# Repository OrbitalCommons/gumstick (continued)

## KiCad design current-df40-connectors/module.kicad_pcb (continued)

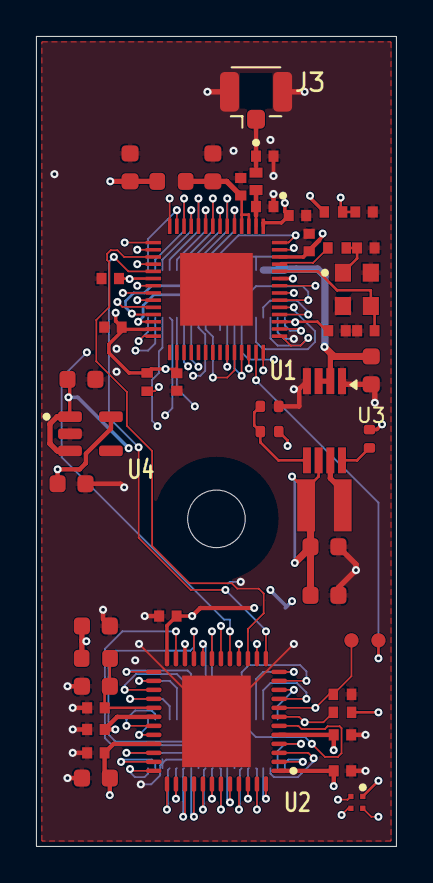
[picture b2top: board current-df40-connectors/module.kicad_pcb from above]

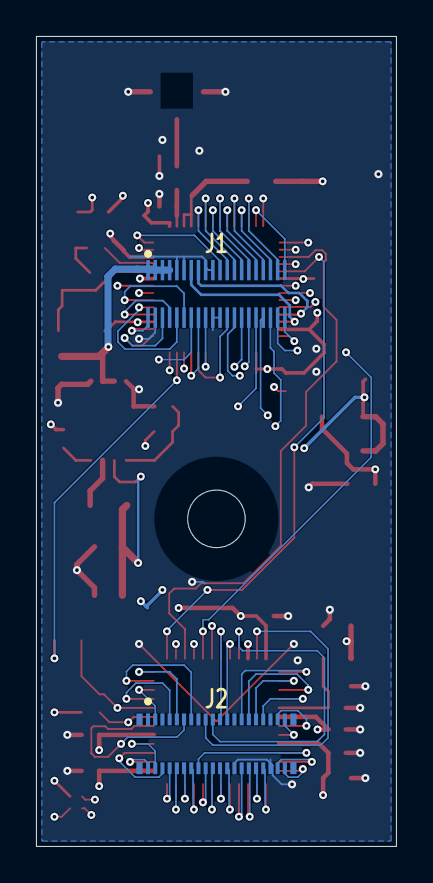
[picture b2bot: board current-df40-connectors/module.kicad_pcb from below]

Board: 4 copper layers, 20.0 x 45.0 mm, 52 parts (2 on the bottom side), 84 nets.

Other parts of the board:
H1: MountingHole_3.2mm_M3

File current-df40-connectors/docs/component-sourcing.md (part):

# Component sourcing

Catalog identities checked 2026-09-23 for the current ESP32-S2 module.
All 50 purchased component placements now have a manufacturer part number
and an LCSC product link (21 unique part numbers). Catalog identity and
package size were checked; this is not a reservation of assembly stock.
Confirm JLCPCB assembly availability and the final land patterns before ordering.

## Corrected imported IDs

- U1: C2841141 is ESP32-S2FH2, not the requested 4 MB part. Use C2840995, ESP32-S2FH4.
- Y1: C555614 is a JGHC crystal. The selected ECS-400-10-36-CKY-TR is C2449947.
- L3: the imported manufacturer part number was a ferrite bead. The 2.2 nH RF inductor is Murata LQG15HS2N2S02D, C86061.
- C33/C34/C43/C45: the old 0402 supplier ID no longer matched their 0603 footprints. These now use the same 10 V, 0603 part as C60.
- C61/C67 are now matched 10 V 0603 output capacitors; C62–C66 retain their selected 50 V parts.

## Selected parts

| References | Manufacturer part | LCSC | Specification |
| --- | --- | --- | --- |
| C1, C2 | GJM1555C1H3R3BB01D | [C76906](https://www.lcsc.com/product-detail/C76906.html) | 0402; 3.3 pF; C0G; 50 V |
| C32 | CL05A105KO5NNNC | [C29266](https://www.lcsc.com/product-detail/C29266.html) | 0402; 1 uF; X5R; 16 V |
| C33, C34, C43, C45, C60 | CL10A106KP8NNNC | [C19702](https://www.lcsc.com/product-detail/C19702.html) | 0603; 10 uF; X5R; 10 V |
| C35, C37, C38, C39, C40, C41, C42, C44, C46, C48, C49, C50, C52 | CL05B104KO5NNNC | [C1525](https://www.lcsc.com/product-detail/C1525.html) | 0402; 100 nF; X7R; 16 V |
| C6, C7 | CL05C120JB5NNNC | [C26406](https://www.lcsc.com/product-detail/C26406.html) | 0402; 12 pF; C0G; 50 V |
| C61, C67 | CL10A226MPCNUBE | [C5355402](https://jlcpcb.com/partdetail/6155917-CL10A226MPCNUBE/C5355402) | 0603; 22 uF each; X5R; 10 V; two in parallel |
| C62, C63, C66 | CL10A105KB8NNNC | [C15849](https://www.lcsc.com/product-detail/C15849.html) | 0603; 1 uF; X5R; 50 V |
| D1 | FC-B1010RGBT-HG | [C158099](https://www.lcsc.com/product-detail/C158099.html) | Common-anode RGB; 1.0 x 1.0 mm |
| J1 | DF40C(2.0)-40DS-0.4V(51) | [C597934](https://www.lcsc.com/product-detail/C597934.html) | 40 contacts; 0.4 mm pitch; receptacle |
| L1, L2 | BLM18KG101TN1D | [C160981](https://www.lcsc.com/product-detail/C160981.html) | 0603; ferrite bead; 100 ohm at 100 MHz |
| L3 | LQG15HS2N2S02D | [C86061](https://www.lcsc.com/product-detail/C86061.html) | 0402; 2.2 nH; RF inductor |
| L4 | XFL3012-222MEC | [C3911432](https://www.lcsc.com/product-detail/C3911432.html) | 3 x 3 mm; 2.2 uH |
| R20, R22, R28, R29, R60, R61 | RC0402FR-0710KL | [C60490](https://www.lcsc.com/product-detail/C60490.html) | 0402; 10 kohm; 1% |
| R3 | 0402WGF0000TCE | [C17168](https://www.lcsc.com/product-detail/C17168.html) | 0402; 0 ohm |
| R62 | RC0402FR-07100KL | [C60491](https://www.lcsc.com/product-detail/C60491.html) | 0402; 100 kohm; 1% |
| U1 | ESP32-S2FH4 | [C2840995](https://www.lcsc.com/product-detail/C2840995.html) | QFN56; 7 x 7 mm; 4 MB flash |
| U2 | ICE40UP5K-SG48I | [C2678152](https://www.lcsc.com/product-detail/C2678152.html) | QFN48; industrial temperature grade |
| U3 | TPS62160DGKR | [C60726](https://www.lcsc.com/product-detail/C60726.html) | VSSOP8; exposed leads; R64/R65 set 3.3 V |
| U4 | TLV75512PDBVR | [C2877864](https://www.lcsc.com/product-detail/C2877864.html) | SOT-23-5; 1.2 V LDO |
| Y1 | ECS-400-10-36-CKY-TR | [C2449947](https://www.lcsc.com/product-detail/C2449947.html) | 2520; 40 MHz; CL 10 pF |

AE1 is a purchased Pulse chip antenna, and H1 is
a drilled mounting hole; none is a purchased assembly component. The M3
screw/spacer and mating motherboard connectors belong to the future carrier BOM.

## ESP32-C3 option

The ESP32-C3 is not a pin-compatible substitute: its QFN32 package is 5 x 5 mm,
whereas ESP32-S2FH4 is QFN56, 7 x 7 mm. A change to C3 requires a new footprint,
pin assignment, power/boot review and routing. Its smaller GPIO budget also
requires reviewing the FPGA link and carrier signals. The current files and
BOM retain the S2 until that architecture decision is made.

Sources: [Espressif ESP32-C3 datasheet](https://documentation.espressif.com/esp32-c3_datasheet_en.html),
[Espressif ESP32-S2 datasheet](https://documentation.espressif.com/esp32-s2_datasheet_en.html).

## Chip antenna option

A ceramic chip antenna could free part of the antenna end, but the entire
manufacturer-defined copper keepout, matching network and carrier clearance
must be compared—not just the component body. No antenna substitution or
outline reduction has been made. See [Johanson antenna layout guidance](https://www.johansontechnology.com/docs/3827/Antenna-2450AT1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

## Procurement follow-up

The exact ECS crystal is currently listed out of stock at LCSC.
[DigiKey lists the same ECS part as XC2666CT-ND](https://www.digikey.com/en/products/detail/ecs-inc/ECS-400-1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,
so it can be sourced without changing the crystal circuit. Arrange the
assembler's supported procurement/consignment method before ordering.
The original C555614 (JGHC S2240000101050JY) has similar catalog frequency,
load and package specifications, but is not silently substituted for ECS.

J2 is now the complementary **DF40C-40DP-0.4V(51)** plug, LCSC
[C424643](https://www.lcsc.com/product-detail/C424643.html). The plug is
manufacturer-listed as mating to J1’s receptacle type. Verify current
stock and JLCPCB assembly availability; prior shared J1/J2 sourcing is obsolete.
TP1/TP2 are bare probe pads and require no purchased parts.

## Smaller buck output capacitors — 2026-09-24

C61's former 0805 is replaced by two matched 0603 capacitors, C61/C67. JLCPCB listed 3,154 in stock (2,642 available to order) when checked; stock must be rechecked at order time. Samsung specifies 1.6 × 0.8 × 0.85 mm, 10 V, ±20%, X5R (−55 to +85 °C). Its typical 25 °C DC-bias curve gives about −55% at 3.3 V: about 10 µF each, or 20 µF combined. Applying −20% initial tolerance and −15% temperature variation as a conservative budgeting exercise gives approximately 13.5 µF combined, not a guaranteed manufacturer minimum. TI TPS62162 Table 2 supports 2.2 µH with 10/22/47 µF nominal ceramic outputs; the pair provides margin over a single small 22 µF part. Bench transient/stability validation remains part of prototype validation.

Sources: [Samsung characteristics](https://product.samsungsem.com/mlcc/CL10A226MPCNUB.do), [TI TPS62162](https://www.ti.com/lit/ds/symlink/tps62162.pdf). The sampled manufacturer DC-bias curve is saved in `capacitor-output-selection.json`.

### Minimum capacitor package

Use 0402 or larger capacitors. C35 is restored to Samsung CL05B104KO5NNNC (C1525), 100 nF, 16 V, X7R, 0402, and moved outward to leave fanout space. Prefer moving components outward over shrinking below 0402. Confirm stock at order.

### Antenna Revision B

AE1 is now purchased Pulse ANT2012LL00R2400A (LCSC C3284792; 363 listed in stock on 2026-09-26); J3 is Hirose U.FL-R-SMT-1(01), supplier pending. R63 is a populated 0402 zero-ohm link: UNI-ROYAL 0402WGF0000TCE, C17168 (JLCPCB Basic listing checked 2026-09-26). Final RF tuning remains pending. C68/C69 are DNP 0402 tuning sites. JP1 is an etched cut/bridge selector, not a purchased component. See antenna/INTEGRATION.md for release gates.

## Current RF revision — external only
AE1, JP1, R63, C68 and C69 are removed. Their preceding sourcing history is superseded. J3 remains Hirose U.FL-R-SMT-1(01), supplier ordering ID pending. No chip antenna or chip-tuning components are purchased.

## Crystal replacement — 2026-09-26
Y1 now uses JGHC S2240000101050, C426970, replacing the unavailable ECS part referenced in the historical table above. LCSC lists 1040 and JLCPCB lists 1069. See crystal-replacement.md for footprint and oscillator validation details.

## Inspectable buck update — 2026-09-26

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
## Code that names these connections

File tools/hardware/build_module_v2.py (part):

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
# ESP32-C6 QFN40 (datasheet v1.5 Table 2-1 / 2-4): no in-package flash; SPI0/1 pins 20-22 and 24-26 go to the external W25Q128 (U4).
# The flash runs from the 3.3 V plane (datasheet: VDD_SPI may be left for other use when the flash has its own supply), so pin 23 is
# unconnected: VDD_SPI sits between the flash data pins and its 0.1/1 uF pair would have no room. QFN40 has GPIO10/11 and no GPIO14: CRESET/CDONE move to GPIO10/11, GPIO18 goes to the connector.
esp_names = {'1': 'ANT', '2': 'VDDA3P3', '3': 'VDDA3P3', '4': 'CHIP_PU', '5': 'VDDPST1', '6': 'GPIO0/XTAL_32K_P', '7': 'GPIO1/XTAL_32K_N',
             '8': 'GPIO2/FSPIQ', '9': 'GPIO3', '10': 'GPIO4/MTMS', '11': 'GPIO5/MTDI', '12': 'GPIO6/MTCK/FSPICLK', '13': 'GPIO7/MTDO/FSPID',
             '14': 'GPIO8', '15': 'GPIO9', '16': 'GPIO10', '17': 'GPIO11', '18': 'GPIO12/USB_D-', '19': 'GPIO13/USB_D+', '20': 'SPICS0',
             '21': 'SPIQ', '22': 'SPIWP', '23': 'VDD_SPI', '24': 'SPIHD', '25': 'SPICLK', '26': 'SPID', '27': 'GPIO15', '28': 'VDDPST2',
             '29': 'GPIO16/U0TXD', '30': 'GPIO17/U0RXD', '31': 'GPIO18', '32': 'GPIO19', '33': 'GPIO20', '34': 'GPIO21', '35': 'GPIO22',
             '36': 'GPIO23', '37': 'VDDA1', '38': 'XTAL_N', '39': 'XTAL_P', '40': 'VDDA2', '41': 'GND'}
esp_pins = {'1': 'RF_IN', '2': 'ESP_VDD3P3', '3': 'ESP_VDD3P3', '4': 'ESP_EN', '5': '+3.3V', '6': 'FPGA_SPI_IO3', '7': 'FPGA_SPI_MOSI',
            '8': 'FPGA_SPI_CS_N', '9': 'FPGA_SPI_SCK', '10': 'ESP_GPIO4', '11': 'ESP_GPIO5', '12': 'FPGA_SPI_MISO', '13': 'FPGA_SPI_IO2',
            '14': 'ESP_GPIO8', '15': 'ESP_GPIO9_BOOT', '16': 'FPGA_CRESET_N', '17': 'FPGA_CDONE', '18': 'USB_D-', '19': 'USB_D+', '20': 'FLASH_CS',
            '21': 'FLASH_DO', '22': 'FLASH_WP', '24': 'FLASH_HD', '25': 'FLASH_CLK', '26': 'FLASH_DI', '27': 'ESP_GPIO15',
            '28': '+3.3V', '29': 'ESP_GPIO16_TXD', '30': 'ESP_GPIO17_RXD', '31': 'ESP_GPIO18', '32': 'ESP_GPIO19', '33': 'ESP_GPIO20',
            '34': 'ESP_GPIO21', '35': 'ESP_GPIO22', '36': 'ESP_GPIO23', '37': '+3.3V', '38': 'XTAL_N', '39': 'XTAL_P', '40': '+3.3V', '41': 'GND'}
esp_types = {k: ('power_in' if n in ('VDDA3P3', 'VDDPST1', 'VDDPST2', 'VDDA1', 'VDDA2', 'GND') else 'power_out' if n == 'VDD_SPI' else 'input' if n in ('CHIP_PU',) else 'passive' if n in ('ANT', 'XTAL_N', 'XTAL_P') else 'bidirectional') for k, n in esp_names.items()}
add('U1', 'ESP32-C6', stdfp('Package_DFN_QFN', 'QFN-40-1EP_5x5mm_P0.4mm_EP3.6x3.6mm', 'QFN-40-1EP_5x5mm_P0.4mm_EP3.3x3.3mm'),
    esp_pins, U1X, U1Y, 0, 'ic', 'ESP32-C6', 'C5364646', esp_names, esp_types)
# 16 MB quad SPI NOR (W25Q128JVPIQ, WSON-8 6x5) in the north-east corner, rotated so DI/CLK/HOLD/VCC face the channel from U1
flash_names = {'1': '/CS', '2': 'DO(IO1)', '3': '/WP(IO2)', '4': 'GND', '5': 'DI(IO0)', '6': 'CLK', '7': '/HOLD(IO3)', '8': 'VCC', '9': 'EP'}
flash_pins = {'1': 'FLASH_CS', '2': 'FLASH_DO', '3': 'FLASH_WP', '4': 'GND', '5': 'FLASH_DI', '6': 'FLASH_CLK', '7': 'FLASH_HD', '8': '+3.3V', '9': 'GND'}
flash_types = {'1': 'input', '2': 'bidirectional', '3': 'bidirectional', '4': 'power_in', '5': 'bidirectional', '6': 'input', '7': 'bidirectional', '8': 'power_in', '9': 'passive'}
add('U4', 'W25Q128JVPIQ', stdfp('Package_SON', 'WSON-8-1EP_6x5mm_P1.27mm_EP3.4x4.3mm', 'WSON-8-1EP_6x5mm_P1.27mm_EP3.4x4.3mm'),
    flash_pins, 118.0, 105.3, -90, 'ic', 'W25Q128JVPIQ', 'C190862', flash_names, flash_types)
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fpga_pins = {}
for k, n in fpga_names.items():
    if n.startswith(('IOB_', 'IOT_')) and 'SPI' not in n: fpga_pins[k] = 'FPGA_' + n
fpga_pins.update({'1': '+3.3V', '5': '+1.2V', '7': 'FPGA_CDONE', '8': 'FPGA_CRESET_N', '14': 'FPGA_SPI_MISO', '15': 'FPGA_SPI_SCK', '16': 'FPGA_SPI_CS_N',
                  '17': 'FPGA_SPI_MOSI', '13': 'FPGA_SPI_IO2', '18': 'FPGA_SPI_IO3', '22': '+3.3V', '24': '+3.3V', '29': '+1.2V_PLL', '30': '+1.2V',
                  '33': '+3.3V', '39': 'FPGA_RGB0', '40': 'FPGA_RGB1', '41': 'FPGA_RGB2', 'PAD': 'GND'})
fpga_types = {k: ('power_in' if n in ('VCCIO_2', 'VCC', 'SPI_VCCIO1', 'VPP_2V5', 'VCCPLL', 'VCCIO_0', 'GND') else 'output' if n == 'CDONE' else 'input' if n == 'CRESET_B' else 'bidirectional') for k, n in fpga_names.items()}
add('U2', 'iCE40UP5K-SG48', v1fp('ICE40-QFN', 'ICE40-QFN'), fpga_pins, U2X, U2Y, 180, 'ic', 'ICE40UP5K-SG48I', 'C2678152', fpga_names, fpga_types)

add('Y1', '40MHz / CL10pF', v1fp('Y1_JGHC_S2240000101050', 'Crystal_2520_4pin'), {'IN/OUT': 'XTAL_P_CRYSTAL', 'OUT/IN': 'XTAL_N', 'GND-A': 'GND', 'GND-B': 'GND'},
    110.4, 107.0, 0, 'xtal', 'S2240000101050', 'C426970', {'IN/OUT': 'IN/OUT', 'OUT/IN': 'OUT/IN', 'GND-A': 'GND', 'GND-B': 'GND'})
add('J3', 'U.FL-R-SMT-1(01)', v1fp('J3_U.FL_Hirose_U.FL-R-SMT-1_Vertical', 'UFL_Vertical'), {'1': 'RF_ANT', '2': 'GND'}, 104.95, 106.5, 90, 'connector', 'U.FL-R-SMT-1(01)', '')
add('TP1', 'FPGA_CRESET_N', v1fp('TestPoint_0p8', 'TestPoint_0p8'), {'1': 'FPGA_CRESET_N'}, 116.8, 122.2, 0, 'testpoint', bom=False)
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cap0402('C1', '1.5pF', 'RF_IN', 'GND', 107.0, 111.7154, 90, '', 'GJM1555C1H1R5WB01D')
ind0402('L3', '2.2nH', 'RF_IN', 'RF_ANT', 105.8, 112.2, 180, 'C86061', 'LQG15HS2N2S02D')
cap0402('C2', '1.5pF', 'RF_ANT', 'GND', 104.35, 111.7154, 90, '', 'GJM1555C1H1R5WB01D')
# crystal north of pins 38/39; at 0.4 mm pitch only 0201 parts fit on the pin lines (L5 on XTAL_P, C39 on VDDA1)
ind0201('L5', '24nH', 'XTAL_P', 'XTAL_P_CRYSTAL', 109.6, 110.15, 90, '', 'LQP03TG24NJ02D')
cap0402('C6', '12pF', 'XTAL_P_CRYSTAL', 'GND', 108.3, 107.29, 90, 'C26406')
cap0402('C7', '12pF', 'XTAL_N', 'GND', 112.6, 106.7096, -90, 'C26406')
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cap0402('C37', '0.1uF', '+3.3V', 'GND', 105.9, 114.2846, -90)        # VDDPST1 pin 5, west of the link columns (pad 1 on the pin-5 line)
res0402('R22', '10k', 'ESP_EN', '+3.3V', 105.9, 118.64, 90)
cap0402('C32', '1uF', 'ESP_EN', 'GND', 105.9, 120.6, -90, 'C29266')
cap0402('C38', '0.1uF', '+3.3V', 'GND', 115.35, 111.15, 90)          # VDDPST2 pin 28, north of the GPIO15/TXD/RXD vias
cap0603('C33', '10uF', '+3.3V', 'GND', 114.0, 105.0, 90)
# flash supply decoupling at U4 pin 8 (+3.3V): 0.1 uF (0201) in the pocket between the HOLD drop and the WP/DO/CS columns;
# C33 (10 uF) sits on the same plane 4 mm west of the chip
cap0201('C68', '0.1uF', '+3.3V', 'GND', 119.585, 109.35, 180)       # pad 1 on the pin-8 drop, 1.4 mm from the pin
res0402('R20', '10k', 'ESP_GPIO9_BOOT', '+3.3V', 115.1, 121.0, -90)    # pad 1 north next to the GPIO9 level via
res0402('R21', '10k', 'ESP_GPIO8', '+3.3V', 114.15, 121.3, -90)

# --- 1.2 V regulator cluster west of the FPGA; FPGA decoupling at its pins.
# U2 at (111,130.5) rotation 180: pins 13-24 top (y 127.0), 25-36 left (x 107.5), 37-48 bottom (y 134.0), 1-12 right (x 114.5).
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res0402('R29', '10k', 'FPGA_CDONE', '+3.3V', 119.5, 123.2, 0)

# ---------------------------------------------------------------- M.2 contacts (custom pinout; see docs/icd-v2-pinout.csv)
GND_CONTACTS = [1, 3, 9, 15, 21, 27, 39, 45, 51, 57, 71, 73, 75]   # 33 now carries ESP_GPIO4
PWR_CONTACTS = [2, 4, 70, 72, 74]
# ESP signals ride a B.Cu bus down the east margin to the even (B.Cu) contacts 6..34; order follows the bus nesting.
esp_contacts = {34: 'ESP_EN', 33: 'ESP_GPIO4', 32: 'ESP_GPIO5', 30: 'ESP_GPIO8', 28: 'ESP_GPIO9_BOOT', 26: 'USB_D-', 24: 'USB_D+', 22: 'ESP_GPIO15',
                20: 'ESP_GPIO16_TXD', 18: 'ESP_GPIO17_RXD', 16: 'ESP_GPIO18', 14: 'ESP_GPIO19', 12: 'ESP_GPIO20', 10: 'ESP_GPIO21', 8: 'ESP_GPIO22',
                6: 'ESP_GPIO23'}   # 33 is a front contact reached through its old ground via
rgb_contacts = {}
# FPGA I/O contacts: assign by physical order to keep the fanout uncrossed.
# Right-side pins 1-12 (x fixed, y bottom->top) feed the right odd contacts 11..29 (F.Cu);
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
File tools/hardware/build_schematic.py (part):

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 for x in xs[1:-1]:junction(x,y)
 net_marker(net,xs[0],y)
# Buck input/enable, switch/inductor, feedback, output, power-good pullup.
rail('VIN_5V',[pin('C60',1),(bx(35.56),274.32)],269.24)
path(pin('U3',2),(bx(35.56),269.24));path(pin('U3',3),(bx(35.56),274.32));junction(bx(35.56),269.24)
path(pin('U3',7),pin('L4',1));label('BUCK_SW',bx(72.39),269.24)
path(pin('L4',2),(bx(111.76),269.24),pin('C61',1))
path((bx(111.76),269.24),(bx(132.08),269.24),pin('C67',1));junction(bx(111.76),269.24)
path((bx(132.08),269.24),(167.64,269.24));junction(bx(132.08),269.24);label('+3.3V',167.64,269.24,0,'right bottom')
path(pin('R62',2),(bx(111.76),279.4));junction(bx(111.76),279.4)
path(pin('U3',6),(bx(96.52),274.32),(bx(96.52),269.24));junction(bx(96.52),269.24)
path(pin('U3',8),pin('R62',1));label('PG_3V3',bx(76.2),279.4)
rail('GND',[pin('C60',2),pin('C61',2),pin('C67',2)]+[pin('U3',n) for n in [1,4]],314.96)
# Adjustable buck divider, sensed from the output rail.
path(pin('R64',1),(bx(76.2),287.02));net_marker('+3.3V',bx(76.2),287.02)
path(pin('R64',2),pin('R65',1));junction(bx(76.2),302.26)
path(pin('U3',5),(bx(63.5),302.26),(bx(76.2),302.26));label('BUCK_FB',bx(63.5),302.26)
path(pin('R65',2),(bx(76.2),314.96));junction(bx(76.2),314.96)
# LDO with bypass capacitors and enable tied to its input.
rail('+3.3V',[pin('C62',1),pin('U4',1)],271.78)
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rail('GND',[pin('C62',2),pin('U4',2),pin('C63',2)],307.34)
# ESP_EN reset RC: supply -> pull-up -> enable node, shunt capacitor to ground.
path((50.8,220.98),pin('R22',2));net_marker('+3.3V',50.8,220.98)
path(pin('R22',1),(83.82,220.98),(96.52,220.98));label('ESP_EN',96.52,220.98)
path((83.82,220.98),pin('C32',1));junction(83.82,220.98)
path(pin('C32',2),(83.82,237.49));net_marker('GND',83.82,237.49)
items[-1]=items[-1].replace('(property "Value" "GND"', '(property "Value" "GND" (hide yes)')
# Crystal series link and load capacitors.
path(pin('R3',1),(25.4,162.56));label('XTAL_P',25.4,162.56)
path(pin('R3',2),pin('Y1','IN/OUT'));path(pin('C6',1),(63.5,162.56));junction(63.5,162.56)
label('XTAL_P_CRYSTAL',45.72,162.56)
path(pin('Y1','OUT/IN'),(119.38,162.56),pin('C7',1));path((119.38,162.56),(134.62,162.56));junction(119.38,162.56);label('XTAL_N',134.62,162.56,0,'right bottom')
rail('GND',[pin('C6',2),pin('C7',2),pin('Y1','GND-A'),pin('Y1','GND-B')],190.5)
# Original ESP32 matching directly feeds U.FL, without selector or chip branch.
path(pin('C1',1),(205.74,162.56),pin('L3',1));path((196.85,162.56),(205.74,162.56));junction(205.74,162.56);label('RF_IN',196.85,162.56)
path(pin('L3',2),pin('J3',1));path(pin('C2',1),(245.11,162.56));junction(245.11,162.56);label('RF_ANT',252.73,162.56)
rail('GND',[pin('C1',2),pin('C2',2),pin('J3',2)],190.5)
# Each filter has an input shunt capacitor, series inductor, and output shunts.
for ind,cin,cout,cbypass,x,y,vin,vout in filter_groups:
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
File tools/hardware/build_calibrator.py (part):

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# Sixteen switch channels; remaining clock-capable pin reserved for PPS.
display_contacts=[2,4,5,6,7,10,11,12,14,15,16,17,19,20,21,24]
display_signals=[contract['J2']['pins'][str(n)] for n in display_contacts]
used_esp={'VIN_5V','GND','USB_D+','USB_D-','ESP_EN','ESP_GPIO0_BOOT','ESP_GPIO43_TXD','ESP_GPIO44_RXD','ESP_GPIO38','ESP_GPIO21'}
used_fpga={'GND',*display_signals,'FPGA_IOT_46B_G0','FPGA_IOT_50B'}
for ref,y in [('J1',44),('J2',69)]:
 c=contract[ref];pins={k:(n if n in (used_esp if ref=='J1' else used_fpga) else None) for k,n in c['pins'].items()}
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 capacitor('C2' if ref=='U2' else 'C6','4.7uF','VIN_5V','GND',x-4,y,90,'C19666')
 capacitor('C3' if ref=='U2' else 'C7','4.7uF',rail,'GND',x+4,y,90,'C19666')
resistor('R3','2.2k','VIN_5V','POWER_LED',177,49,lcsc='C4190');led('D1','POWER_LED','GND',181,49,'POWER')
add('SW1','BOOT / RUN',std('Button_Switch_SMD','SW_SPDT_CK_JS102011SAQN'),{'1':'GND','2':'ESP_GPIO0_BOOT','3':None},181,61,0,'C221660','JS102011SAQN',kind='switch')
add('SW2','RESET',std('Button_Switch_SMD','SW_SPST_TL3342'),{'1':'GND','2':'ESP_EN'},181,73,0,'C2886898','TL3342F160QG',kind='switch')
resistor('R4','100k','ESP_GPIO0_BOOT','+3V3_LOGIC',174,58,lcsc='C25803')
text('BOOT / RUN',181,55,.8);text('RESET',181,78,.8)
# Four identical optical rows. Each LED gets its own 1% resistor.
# Identical branch geometry and a low-resistance 5V distribution plane control supply droop.
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 add('U'+str(3+bank),'SN74LVC541APWR',std('Package_SO','TSSOP-20_4.4x6.5mm_P0.65mm'),pins,x,24,90,'C113281','SN74LVC541APWR',names=names,types=types)
 capacitor('C'+str(4+bank),'100nF','+3V3_LOGIC','GND',x+5.5,24,90)
# GNSS: UART from ESP32, PPS to both processors; trigger to FPGA and receiver EXTINT.
gpspins={'1':'GND','2':'ESP_GPIO44_RXD','3':'ESP_GPIO43_TXD','4':'GPS_PPS','5':'TRIGGER_3V3','6':'+3V3_GPS','7':'+3V3_GPS','8':'+3V3_GPS','9':None,'10':'GND','11':'GNSS_RF','12':'GND','13':None,'14':None,'15':None,'16':None,'17':None,'18':None}
gpsnames=dict(zip(map(str,range(1,19)),['GND','TXD','RXD','TIMEPULSE','EXTINT','V_BCKP','V_IO','VCC','RESET_N','GND','RF_IN','GND','LNA_EN','VCC_RF','RESERVED','RESERVED','SDA','SCL']))
add('U6','MAX-M10S-00B-01',std('RF_GPS','ublox_MAX'),gpspins,187,96,0,'C24834155','MAX-M10S-00B-01',names=gpsnames)
capacitor('C8','100nF','+3V3_GPS','GND',179,95,90)
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capacitor('C10','10nF','ANT_BIAS','GND',195,89,0,'C1589')
# Use clock input G0 for PPS. Small series resistors separate destinations and aid probing.
resistor('R6','100R','GPS_PPS','FPGA_IOT_46B_G0',172,92,lcsc='C22775')
resistor('R7','100R','GPS_PPS','ESP_GPIO38',172,96,lcsc='C22775')
# External trigger is 3.3/5V logic input, not a 50-ohm terminated analog input.
add('J6','TRIGGER / PPS',std('Connector_PinHeader_2.54mm','PinHeader_1x04_P2.54mm_Vertical'),{'1':'GND','2':'TRIGGER_IN','3':'GND','4':'PPS_MON'},142,100,90,kind='connector',bom=False)
add('U7','SN74LVC1G17DBVR',std('Package_TO_SOT_SMD','SOT-23-5'),{'1':None,'2':'TRIGGER_LIMIT','3':'GND','4':'TRIGGER_3V3','5':'+3V3_LOGIC'},158,94,lcsc='C7836',names={'1':'NC','2':'A','3':'GND','4':'Y','5':'VCC'})
resistor('R8','1k','TRIGGER_IN','TRIGGER_LIMIT',153,94)
resistor('R9','100k','TRIGGER_LIMIT','GND',153,98,lcsc='C25803')
resistor('R80','100R','TRIGGER_3V3','FPGA_IOT_50B',164,98,lcsc='C22775')
resistor('R81','100R','TRIGGER_3V3','ESP_GPIO21',164,101,lcsc='C22775')
resistor('R82','100R','GPS_PPS','PPS_MON',161,105,lcsc='C22775')
capacitor('C11','100nF','+3V3_LOGIC','GND',158,90)
for i in range(4):add('C'+str(60+i),'10uF',std('Capacitor_SMD','C_0805_2012Metric'),{'1':'VIN_5V','2':'GND'},174+i*5,39,lcsc='C15850',mpn='CL21A106KAYNNNE',kind='c')
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
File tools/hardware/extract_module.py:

#!/usr/bin/env python3
"""Extract auditable module connectivity from the saved native reference netlist."""
from pathlib import Path
import xml.etree.ElementTree as E
import json,csv
ROOT=Path(__file__).resolve().parents[2]
r=E.parse(ROOT/'docs/hardware/original-netlist.xml').getroot()
cs={c.get('ref'):c for c in r.find('components')}
libs={p.get('part'):p for p in r.find('libparts')}
nets={}
for n in r.find('nets'):
 for p in n.findall('node'):
  nets[p.get('ref'),p.get('pin')]=None if n.get('name').startswith('unconnected-') else n.get('name')
eagle=json.loads((ROOT/'docs/hardware/eagle-pad-nets.json').read_text())
for (ref,pin),net in list(nets.items()):
 original=eagle.get(f'{ref}.{pin}')
 if original and not original.startswith('N$'):nets[ref,pin]=original
refs=['U1','U2','U5','U$1','L1','L2','L3','R3','R20','R22','R28','R29','C1','C2','C6','C7','C32','C33','C34','C35']+[f'C{i}' for i in range(37,51) if f'C{i}' in cs]+['C52']
# C47 is a core rail decoupler? All candidate two-terminal parts must belong to retained rails.
parts={}
rename={'U$1':'AE1','U5':'Y1'}
netrename={'ESP_38':'ESP_GPIO34','ESP_39':'ESP_GPIO35','GPS_RESET':'ESP_GPIO33','CPU_LED':'ESP_GPIO2','GPS-RX':'ESP_TXD','GPS-TX':'ESP_RXD','GPS-PPS':'PPS','Net-(C6-Pad1)':'XTAL_P_CRYSTAL','+5V':'VIN_5V'}
for ref in refs:
 c=cs[ref]; lp=libs[c.find('libsource').get('part')]
 pins={p.get('num'):{'name':p.get('name'),'type':p.get('type'),'net':netrename.get(nets.get((ref,p.get('num'))),nets.get((ref,p.get('num'))))} for p in lp.find('pins')}
 parts[rename.get(ref,ref)]={'source_ref':ref,'value':c.findtext('value'),'footprint':c.findtext('footprint'),'pins':pins}
p=parts['U1']['pins']
for i in [29,31,32,33,34,35,36]:p[str(i)]['net']=None
for pin,gpio in {6:1,8:3,9:4,10:5,11:6,12:7,13:8,21:15,22:16,23:17,24:18,28:21,43:39,44:40,46:41,47:42}.items():p[str(pin)]['net']=f'ESP_GPIO{gpio}'
p['50']['net']=None;p['55']['net']=None  # Internal reset pull-downs; no external straps.
parts['U1']['value']='ESP32-S2FH4';parts['U2']['value']='iCE40UP5K-SG48';parts['Y1']['value']='40MHz / CL10pF'
def add(ref,value,footprint,pins):
 parts[ref]={'value':value,'footprint':footprint,'pins':{str(i):{'name':name,'net':net,'type':typ} for i,name,net,typ in pins}}
def passive(ref,value,a,b,kind='R',footprint=None):
 fp=footprint or {'R':'Resistor_SMD:R_0402_1005Metric','C':'Capacitor_SMD:C_0603_1608Metric','L':'Inductor_SMD:L_0402_1005Metric'}[kind]
 add(ref,value,fp,[(1,'1',a,'passive'),(2,'2',b,'passive')])
add('U3','TPS62162DSGR','Package_SON:WSON-8-1EP_2x2mm_P0.5mm_EP0.9x1.6mm',[(1,'PGND','GND','power_in'),(2,'VIN','VIN_5V','power_in'),(3,'EN','VIN_5V','input'),(4,'AGND','GND','power_in'),(5,'FB','GND','input'),(6,'VOS','+3.3V','input'),(7,'SW','BUCK_SW','power_out'),(8,'PG','PG_3V3','open_collector'),(9,'EP','GND','power_in')])
add('U4','TLV75512PDBVR','Package_TO_SOT_SMD:SOT-23-5',[(1,'IN','+3.3V','power_in'),(2,'GND','GND','power_in'),(3,'EN','+3.3V','input'),(4,'NC',None,'no_connect'),(5,'OUT','+1.2V','power_out')])
passive('L4','2.2uH / Isat >= 1.9A','BUCK_SW','+3.3V','L','Module:L_XFL3012_222MEC')
passive('C60','10uF / 10V','VIN_5V','GND','C','Capacitor_SMD:C_0805_2012Metric');passive('C61','22uF / 10V','+3.3V','GND','C','Capacitor_SMD:C_0805_2012Metric')
passive('C62','1uF / 6.3V','+3.3V','GND','C');passive('C63','1uF / 6.3V','+1.2V','GND','C');passive('R62','100kR','PG_3V3','+3.3V')
# Explicit carrier interface, provisional physical pin assignments pending footprint/mate review.
j1=['VIN_5V','VIN_5V','VIN_5V','VIN_5V','GND','GND','USB_D-','USB_D+','GND','GND','CHIP_PU','GPIO0','ESP_TXD','ESP_RXD','GND','PPS','ESP_GPIO1','ESP_GPIO2','ESP_GPIO3','ESP_GPIO4','GND','ESP_GPIO5','ESP_GPIO6','ESP_GPIO7','ESP_GPIO8','GND','ESP_GPIO15','ESP_GPIO16','ESP_GPIO17','ESP_GPIO18','GND','ESP_GPIO21','ESP_GPIO33','ESP_GPIO34','ESP_GPIO35','GND','ESP_GPIO39','ESP_GPIO40','ESP_GPIO41','ESP_GPIO42']
j2=['GND','HQ_OSC','GND','BIT0','BIT1','BIT2','BIT3','GND','BIT4','BIT5','BIT6','BIT7','GND','BIT8','BIT9','BIT10','BIT11','GND','BIT12','BIT13','BIT14','BIT15','GND','F2','F3','F4','F6','GND','F9','F10','F19','F20','GND','F23','F25','EXT_33','EXT_EN','RGB_0','RGB_1','RGB_2']
# Connector positions follow routing, not GPIO numbering (carrier pinout revision 2).
j1[19],j1[27]=j1[27],j1[19]
for ref,ns in [('J1',j1),('J2',j2)]:
 assert len(ns)==40
 add(ref,'DF40C(2.0)-40DS-0.4V(51)','Module:DF40C_40DS_2mm',[(i,str(i),n,'passive') for i,n in enumerate(ns,1)])
parts['J2']['value']='DF40C-40DP-0.4V(51)'
parts['J2']['footprint']='Module:J2_DF40C_40DP'
# Original passives use source footprints, resized only for bulk ceramic capacitors.
for ref,c in parts.items():
 if ref.startswith('C') and c['value'].startswith('10u'):c['footprint']='Capacitor_SMD:C_0603_1608Metric'
 if ref.startswith('R') and c['value'].endswith('k'):c['value']+='R'
 if ref=='R3':c['value']='0R'
from devboard_names import apply
name_changes=apply(parts)
j1=[name_changes.get(n,n) for n in j1];j2=[name_changes.get(n,n) for n in j2]
# Preserve the reviewed carrier-contact assignments when re-extracting sources.
override_path=ROOT/'current-df40-connectors/docs/pinout-overrides.json'
if override_path.exists():
 for ref,mapping in json.loads(override_path.read_text()).items():
  ns=j1 if ref=='J1' else j2
  for pin,net in mapping.items():
   parts[ref]['pins'][pin]['net']=net;ns[int(pin)-1]=net
# All extracted source pins are kept, even where carrier circuitry was deliberately removed.
out=ROOT/'current-df40-connectors/docs';out.mkdir(parents=True,exist_ok=True)
(out/'signal-name-map.json').write_text(json.dumps(name_changes,indent=2)+'\n')
(out/'module-connectivity.json').write_text(json.dumps(parts,indent=2)+'\n')
with (out/'carrier-pinout.csv').open('w') as f:
 w=csv.writer(f);w.writerow(['Connector','Pin','Signal','Direction / constraint'])
 for ref,ns in [('J1',j1),('J2',j2)]:
  for i,n in enumerate(ns,1):w.writerow([ref,i,n,'5V input; all four VIN contacts required' if n=='VIN_5V' else 'Ground' if n=='GND' else '3.3V logic; no 5V tolerance' if not (n or '').startswith('USB') else 'USB 2.0 full speed differential pair'])
print(f'{len(parts)} components; {len(set(p["net"] for c in parts.values() for p in c["pins"].values())-{None})} nets')

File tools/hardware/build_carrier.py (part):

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capacitor('C1','4.7uF','VIN_5V','GND',76,31,90,'C19666');capacitor('C2','4.7uF','+3V3_TEST','GND',84,31,90,'C19666');capacitor('C3','100nF','VBUS','GND',104,31,90)
resistor('R3','2.2kR','VIN_5V','P5_LED',70,28,0,'C4190');led('D1','P5_LED','GND',73,28,'5V')
resistor('R4','1kR','+3V3_TEST','P3_LED',70,35);led('D2','P3_LED','GND',73,35,'3V3 TEST')
add('SW1','BOOT / RUN',std('Button_Switch_SMD','SW_SPDT_CK_JS102011SAQN'),{'1':'GND','2':'ESP_GPIO0_BOOT','3':None},65,47,0,'C221660','JS102011SAQN',kind='switch')
for ref,signal,x,y,label in [('SW2','ESP_EN',65,60,'RESET'),('SW3','GPIO46_TEST',130,35,'GPIO46 INPUT')]:
 add(ref,label,std('Button_Switch_SMD','SW_SPST_TL3342'),{'1':'GND' if ref=='SW2' else '+3V3_TEST','2':signal},x,y,0,'C2886898','TL3342F160QG',kind='switch');text(label,x,y+5.5,.9)
resistor('R5','1kR','GPIO46_TEST','ESP_GPIO46',135,41)
text('BOOT       RUN',65,43,.85);text('FLASH: BOOT, tap RESET',53,70,.9,left=True);text('Then RUN, tap RESET',53,72,.9,left=True)
# LEDs: eight regular groups + 3 dedicated sink-driven RGB monitor channels.
esp=[n for n in pinout['J1'].values() if n.startswith('ESP_')]
esp=sorted(set(esp),key=lambda s:(s!='ESP_EN',int(re.search(r'GPIO(\d+)',s).group(1)) if 'GPIO' in s else -1))
fpga=sorted({n for n in pinout['J2'].values() if n.startswith('FPGA_') and 'RGB' not in n},key=lambda s:(0 if 'IOB' in s else 1,int(re.search(r'_(\d+)',s).group(1))))
groups=[('ESP',esp[i:i+8],x,y) for i,x,y in [(0,32,92),(8,69,92),(16,32,133),(24,69,133)]]
groups += [('FPGA',fpga[i:i+8],x,y) for i,x,y in [(0,116,92),(8,153,92),(16,116,133),(24,153,133)]]
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 text(bank+' '+str(bi%4+1) if bank!='RGB' else 'RGB (LOW = ON)',x+6,y-16,1)
 for k,n in enumerate(signals):
  idx=bi*8+k;yy=y-10.5+3*k;rr='R'+str(10+idx);rp='R'+str(110+idx);dd='D'+str(10+idx);active_low=bank=='RGB'
  resistor(rp,'100kR',n,'+3V3_TEST' if active_low or n=='ESP_GPIO0_BOOT' else 'GND',x-7,yy,0,'C25803')
  resistor(rr,'1kR',('+3V3_TEST' if active_low else 'BUF_'+n),'LED_'+n,x+9,yy)
  label=n.replace('ESP_','').replace('FPGA_','').replace('GPIO','IO')
  led(dd,'LED_'+n,'BUF_'+n if active_low else 'GND',x+13,yy,label,red=active_low)
  channels.append({'signal':n,'buffer':ref,'input':k+2,'output':18-k,'led':dd,'resistor':rr,'bias':rp,'active_low':active_low,'bank':bank})
# A usable test fixture can also probe the inputs on exposed labeled LED-bank pull resistor pads.
text('ESP32 + FPGA / PROGRAM & GPIO TEST',100,156,1.5)
text('Power OFF before mating   |   Green: HIGH   Red RGB: LOW   |   GPIO46 input only',100,159,.9)
text('USB programming: BOOT + RESET, then RUN + RESET',100,162,.9)
# Save sources (routing is a separate step, so rerunning does not silently clobber routed production).
(D/'docs/circuit.json').write_text(json.dumps(parts,indent=2)+'\n');(D/'docs/led-map.json').write_text(json.dumps(channels,indent=2)+'\n')
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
